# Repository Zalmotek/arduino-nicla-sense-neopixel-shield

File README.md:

# arduino-nicla-sense-neopixel-shield

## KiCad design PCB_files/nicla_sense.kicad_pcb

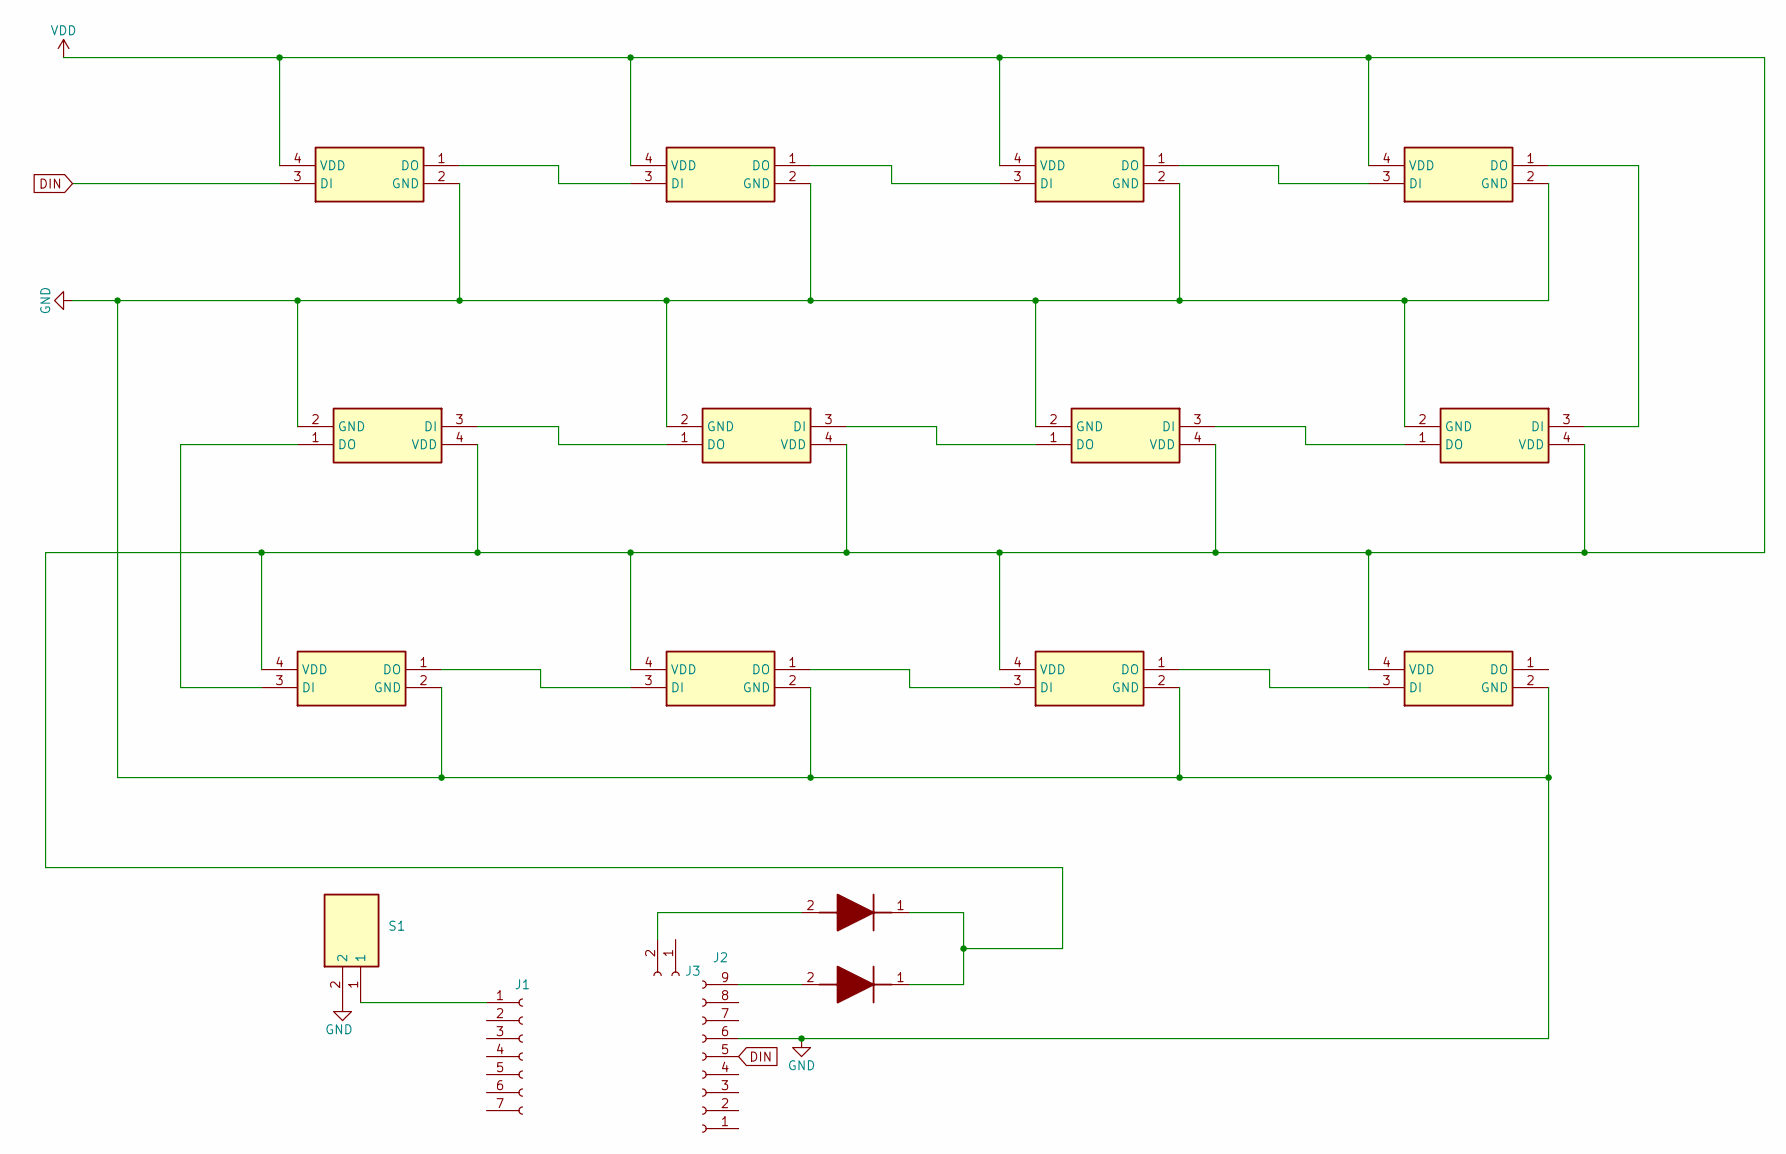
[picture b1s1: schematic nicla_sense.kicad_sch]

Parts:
D1, D2: DIODE; SBRT05U20LPS7B; Mouser Part Number 621-SBRT05U20LPS-7B
J1: Conn_01x07_Female; PinHeader_1x07_P2.54mm_Vertical
J2: Conn_01x09_Female; PinHeader_1x09_P2.54mm_Vertical
J3: Conn_01x02_Female; PinHeader_1x02_P2.54mm_Vertical
S1: B3AL-1005P; B3AL1005P; Manufacturer_Part_Number B3AL-1005P; DIGI-KEY_PART_NUMBER P19888CT-ND
U1, U2, U3, U4, U5, U6, U7, U8, U9, U10, U11, U12: WS2812-2020; 4684; Mouser Part Number 485-4684

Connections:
DIN: J2.5, U1.3 (DI)
GND: J2.6, S1.2, U1.2 (GND), U2.2 (GND), U3.2 (GND), U4.2 (GND), U5.2 (GND), U6.2 (GND), U7.2 (GND), U8.2 (GND), U9.2 (GND), U10.2 (GND), U11.2 (GND), U12.2 (GND)
unnamed: D1.2 (A), J3.2
unnamed: D2.2 (A), J2.9
unnamed: J1.1, S1.1
unnamed: U1.1 (DO), U2.3 (DI)
unnamed: U2.1 (DO), U3.3 (DI)
unnamed: U3.1 (DO), U4.3 (DI)
unnamed: U4.1 (DO), U5.3 (DI)
unnamed: U5.1 (DO), U6.3 (DI)
unnamed: U6.1 (DO), U7.3 (DI)
unnamed: U7.1 (DO), U8.3 (DI)
unnamed: U8.1 (DO), U9.3 (DI)
unnamed: U9.1 (DO), U10.3 (DI)
unnamed: U10.1 (DO), U11.3 (DI)
unnamed: U11.1 (DO), U12.3 (DI)
VDD: D1.1 (K), D2.1 (K), U1.4 (VDD), U2.4 (VDD), U3.4 (VDD), U4.4 (VDD), U5.4 (VDD), U6.4 (VDD), U7.4 (VDD), U8.4 (VDD), U9.4 (VDD), U10.4 (VDD), U11.4 (VDD), U12.4 (VDD)

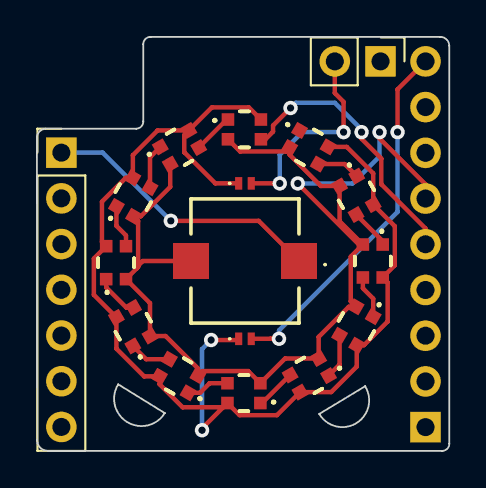
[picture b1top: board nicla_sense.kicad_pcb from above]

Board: 2 copper layers, 22.9 x 23.0 mm, 18 parts (0 on the bottom side), 17 nets.
